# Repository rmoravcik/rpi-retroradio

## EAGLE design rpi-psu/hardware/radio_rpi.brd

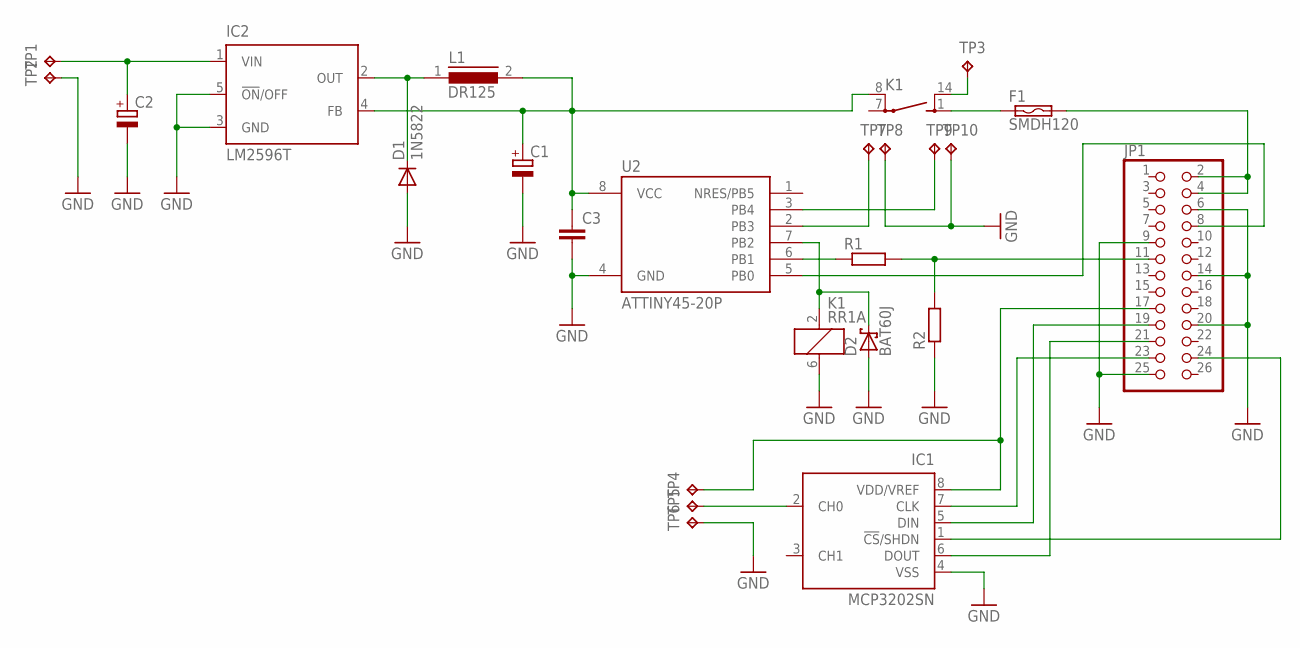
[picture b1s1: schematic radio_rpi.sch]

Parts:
C1: CPOL-EUUD-6,3X7,7; UD-6,3X7,7_NICHICON
C2: CPOL-EUUD-10X10; UD-10X10_NICHICON
C3: C-EUC1206K; C1206K
D1: 1N5822; DO201-15
D2: BAT60J; SOD323_ST
F1: SMDH120; SMD050F
IC1: MCP3202SN; SO-08
IC2: LM2596T; T05D
JP1: PINHD-2X13; 2X13
K1: RR1A
L1: DR125
R1, R2: R-EU_M1206; M1206
TP1, TP2, TP3, TP4, TP5, TP6, TP7, TP8, TP9, TP10: TPTP20SQ; TP20SQ
U2: ATTINY45-20P; PDIP08_300MIL

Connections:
GND: C1.-, C2.-, C3.2, D1.A, D2.A, IC1.4 (VSS), IC2.3 (GND), IC2.5 (!ON!/OFF), JP1.6, JP1.9, JP1.14, JP1.20, JP1.25, K1.6 (2), R2.1, TP2.TP, TP6.TP, TP8.TP, TP10.TP, U2.4 (GND)
unnamed: F1.1, K1.1 (S)
unnamed: F1.2, JP1.2, JP1.4
unnamed: C1.+, C3.1, IC2.4 (FB), K1.8, L1.2, U2.8 (VCC)
unnamed: IC1.1 (!CS!/SHDN), JP1.24
unnamed: IC1.5 (DIN), JP1.19
unnamed: IC1.8 (VDD/VREF), JP1.17, TP4.TP
unnamed: IC1.7 (CLK), JP1.23
unnamed: IC1.2 (CH0), TP5.TP
unnamed: IC1.6 (DOUT), JP1.21
unnamed: JP1.8, U2.5 (PB0)
unnamed: JP1.11, R1.2, R2.2
unnamed: D2.C, K1.2 (1), U2.7 (PB2)
unnamed: R1.1, U2.6 (PB1)
unnamed: K1.14 (S), TP3.TP
unnamed: C2.+, IC2.1 (VIN), TP1.TP
unnamed: TP7.TP, U2.2 (PB3)
unnamed: D1.C, IC2.2 (OUT), L1.1
unnamed: TP9.TP, U2.3 (PB4)

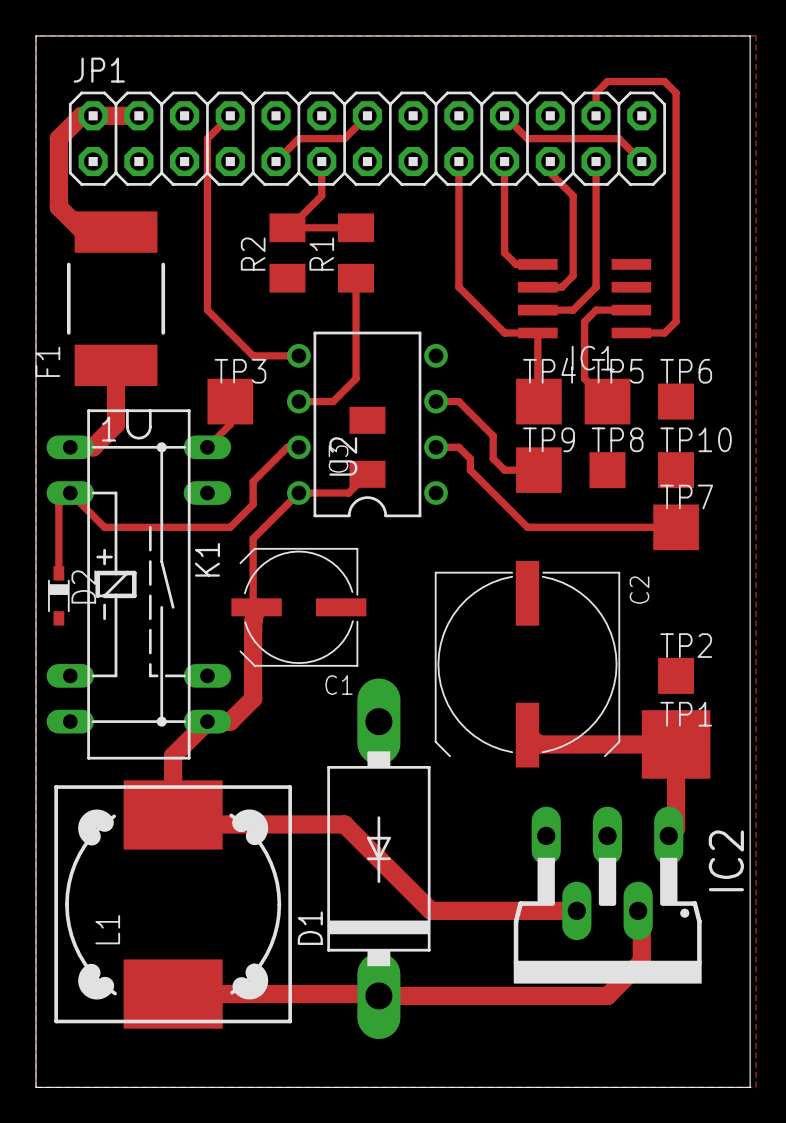
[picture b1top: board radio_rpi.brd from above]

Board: 2 copper layers, 39.7 x 58.4 mm, 24 parts (0 on the bottom side), 19 nets.

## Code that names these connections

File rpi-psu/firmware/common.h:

/*
 *  rpi-psu-1.0
 *  Copyright (C) 2015 Roman Moravcik
 *
 *  This program is free software; you can redistribute it and/or modify
 *  it under the terms of the GNU General Public License as published by
 *  the Free Software Foundation; either version 2 of the License, or
 *  (at your option) any later version.
 *
 *  This program is distributed in the hope that it will be useful,
 *  but WITHOUT ANY WARRANTY; without even the implied warranty of
 *  MERCHANTABILITY or FITNESS FOR A PARTICULAR PURPOSE.  See the
 *  GNU General Public License for more details.
 *
 *  You should have received a copy of the GNU General Public License
 *  along with this program; if not, write to the Free Software
 *  Foundation, Inc., 59 Temple Place, Suite 330, Boston, MA  02111-1307  USA
 */

#ifndef COMMON_H
#define COMMON_H

#include <avr/io.h>

#define TRUE				1
#define FALSE				0

#define RPI_RUNNING_IND			PB0
#define RPI_POWER_OFF_REQ		PB1
#define RELAY				PB2
#define PA_CONTROL			PB3
#define POWER_SWITCH			PB4

#endif // COMMON_H

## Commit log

2016-05-08 Added schematics and source code of FW
2016-05-08 Added measure.cpp by Peter Tellenbach.
2016-05-08 Added first version of not working daemon.
2016-05-10 Interrupt verion finally working.
2016-05-10 First working RPi daemon.
2016-05-10 Rename daemon to rpi-psud
